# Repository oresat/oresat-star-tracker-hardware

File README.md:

# oresat-star-tracker

This is the repository for all things related to the star tracker system for OreSat. The star tracker takes pictures of the local star field and returns the spacecraft's attitude (which way it's pointed). This is critical for both OreSat Live and the Cirrus Flux Camera missions which require the satellite to be pointed down to a specific location on the ground.

Our hardware is all custom hardware for the open source "OreSat bus" that we're developing. The star tracker is one of our [Octavo OSD3358-1G-ISM](https://octavosystems.com/octavo_products/osd335x-sm/) "Linux box on a Chip" cards, with a custom camera setup based on the [On Semiconductor AR1030](https://www.onsemi.com/pub/Collateral/AR0130CS-D.PDF).

*Looking for what's running on this? Our star tracker software, based on [OpenStarTracker](https://openstartracker.org) from the University at Buffalo, was migrated to the [oresat-star-tracker-software](https://github.com/oresat/oresat-star-tracker-software) repository on 2/21/2020.*
"Looking for pru kernel module / firmware see [oresat-linux-prucam](https://github.com/oresat/oresat-linux-prucam)"

Where to find things:

- oresat-camera-hardware - directories related to hardware for OreSat camera system
- Old stuff
   - STM32F4-camera-system - OreSat camera system based on the STM32F4 MCU
   - archive - old files and projects no longer in use
   - camera_testing - files related to testing our AR0130-based cameras

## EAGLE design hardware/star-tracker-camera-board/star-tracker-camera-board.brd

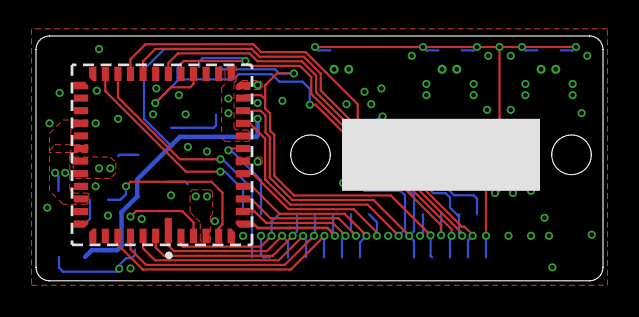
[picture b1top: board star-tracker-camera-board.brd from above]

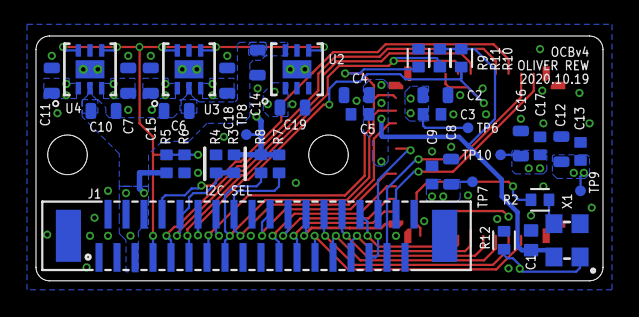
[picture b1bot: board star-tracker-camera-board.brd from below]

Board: 4 copper layers, 31.5 x 13.6 mm, 41 parts (40 on the bottom side), 34 nets.

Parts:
C1: 10nF; .0402-A-NOSILK
C2, C4, C8, C12, C16: 10uF; .0603-C-NOSILK
C3, C5, C9, C13, C17: 0.1uF; .0402-B-NOSILK
C6, C10, C14: 1.0uF; .0603-C-NOSILK
C7, C11, C15, C18, C19: 2.2uF; .0603-C-NOSILK
J1: 3-1734742-6; TE_3-1734742-6
R2: 100; .0402-B
R3, R6: DNP; .0402-B-NOSILK
R4, R5: 10k; .0402-B-NOSILK
R7, R8: 4.7k; .0402-B-NOSILK
R9, R10, R11, R12: 10k; .0402-B
TP6, TP7, TP8, TP9, TP10: TPTP06R; TP06R
U1: AR0134CSSM00SPCA0
U2: TPS70618DRVR; DRV6_1P6X1
U3, U4: TPS71928-28DRVT; DRV6_1P6X1
X1: KC2520B27.0000C10E00; OSC_KYOCERA_KC2520B

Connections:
3.3V: C6.1, C10.1, C14.1, J1.4, J1.5, J1.6, R5.1, U2.6, U3.2, U4.2
!OE: J1.11, R11.1, U1.23
!RESET: J1.13, R9.2, U1.17
CLK_EN: J1.14, R12.2, X1.1
D0: J1.25, U1.45
D1: J1.26, U1.46
D2: J1.27, U1.47
D3: J1.28, U1.48
D4: J1.29, U1.1
D5: J1.30, U1.2
D6: J1.31, U1.3
D7: J1.24, U1.7
D8: J1.23, U1.8
D9: J1.22, U1.9
D10: J1.21, U1.10
D11: J1.20, U1.11
FLASH: J1.9, U1.26
GND: C1.1, C2.2, C3.2, C4.2, C5.2, C6.2, C7.2, C8.2, C9.2, C10.2, C11.2, C12.2, C13.2, C14.2, C15.2, C16.2, C17.2, C18.2, C19.2, J1.1, J1.2, J1.3, J1.17, J1.18, J1.19, J1.35, J1.36, J1.S1, J1.S2, R4.1, R6.2, R9.1, R12.1, U1.6, U1.25, U1.30, U1.35, U1.39, U1.44, U2.2, U2.3, U2.5, U2.7, U2.8, U2.9, U3.5, U3.7, U3.8, U3.9, U4.5, U4.7, U4.8, U4.9, X1.2
HSYNC: J1.34, U1.29
unnamed: R2.1, X1.3
unnamed: R2.2, U1.5
PIXCLK: J1.32, U1.13
SADDR: J1.10, R3.1, R4.2, U1.24
SCLK: J1.16, R7.1, U1.15
SDATA: J1.15, R8.1, U1.16
STANDBY: J1.12, R10.1, U1.22
TRIGGER: J1.8, U1.27
VAA: C11.1, C12.1, C13.1, TP9.TP, U1.34, U1.36, U1.40, U4.1
VAA_PIX: C7.1, C16.1, C17.1, TP10.TP, U1.37, U1.38, U4.3
VDD: C2.1, C3.1, C19.1, TP6.TP, U1.14, U1.19, U2.1
VDD_IO: C1.2, C4.1, C5.1, C18.1, R3.2, R7.2, R8.2, R10.2, R11.2, TP8.TP, U1.12, U1.18, U3.3, X1.4
VDD_PLL: C8.1, C9.1, C15.1, TP7.TP, U1.4, U3.1
VREG_EN: J1.7, R5.2, R6.1, U2.4, U3.4, U3.6, U4.4, U4.6
VSYNC: J1.33, U1.28

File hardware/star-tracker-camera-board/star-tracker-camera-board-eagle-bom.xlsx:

Qty | Value | Device | Package | Parts | Description | DPN | MPN | TP_SIGNAL_NAME | VENDOR
1 | 10nF | C-EU0402-A-NOSILK | .0402-A-NOSILK | C1 | CAPACITOR, European symbol
5 | 10uF | C-EU0603-C-NOSILK | .0603-C-NOSILK | C2, C4, C8, C12, C16 | CAPACITOR, European symbol
5 | 0.1uF | C-EU0402-B-NOSILK | .0402-B-NOSILK | C3, C5, C9, C13, C17 | CAPACITOR, European symbol
3 | 1.0uF | C-EU0603-C-NOSILK | .0603-C-NOSILK | C6, C10, C14 | CAPACITOR, European symbol
5 | 2.2uF | C-EU0603-C-NOSILK | .0603-C-NOSILK | C7, C11, C15, C18, C19 | CAPACITOR, European symbol
1 | 3-1734742-6 | 3-1734742-6 | TE_3-1734742-6 | J1 | 36 Position FFC, FPC Connector Contacts, Vertical, 1 Sided 0.020 (0.50mm) Surfa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 | A100241CT-ND | 3-1734742-6
1 | 100 | R-US_0402-B | .0402-B | R2 | RESISTOR, American symbol
6 | 10k | R-US_0402-B | .0402-B | R4, R5, R9, R10, R11, R12 | RESISTOR, American symbol
2 | 4.7k | R-US_0402-B-NOSILK | .0402-B-NOSILK | R7, R8 | RESISTOR, American symbol
1 | AR0134CSSM00SPCA0 | AR0134CSSM00SPCA0 | AR0134CSSM00SPCA0 | U1
1 | TPS70618DRVR | TPS70618DRVR | DRV6_1P6X1 | U2 |  | 296-48768-1-ND | TPS70618DRVR |  | Texas Instruments
2 | TPS71928-28DRVT | TPS71928-28DRVT | DRV6_1P6X1 | U3, U4 |  | 296-21660-1-ND | TPS71928-28DRVR |  | Texas Instruments
1 | KC2520B27.0000C10E00 | KC2520B27.0000C10E00 | OSC_KYOCERA_KC2520B | X1 |  | 478-4781-1-ND | KC2520B27.0000C10E00 |  | Kyocera

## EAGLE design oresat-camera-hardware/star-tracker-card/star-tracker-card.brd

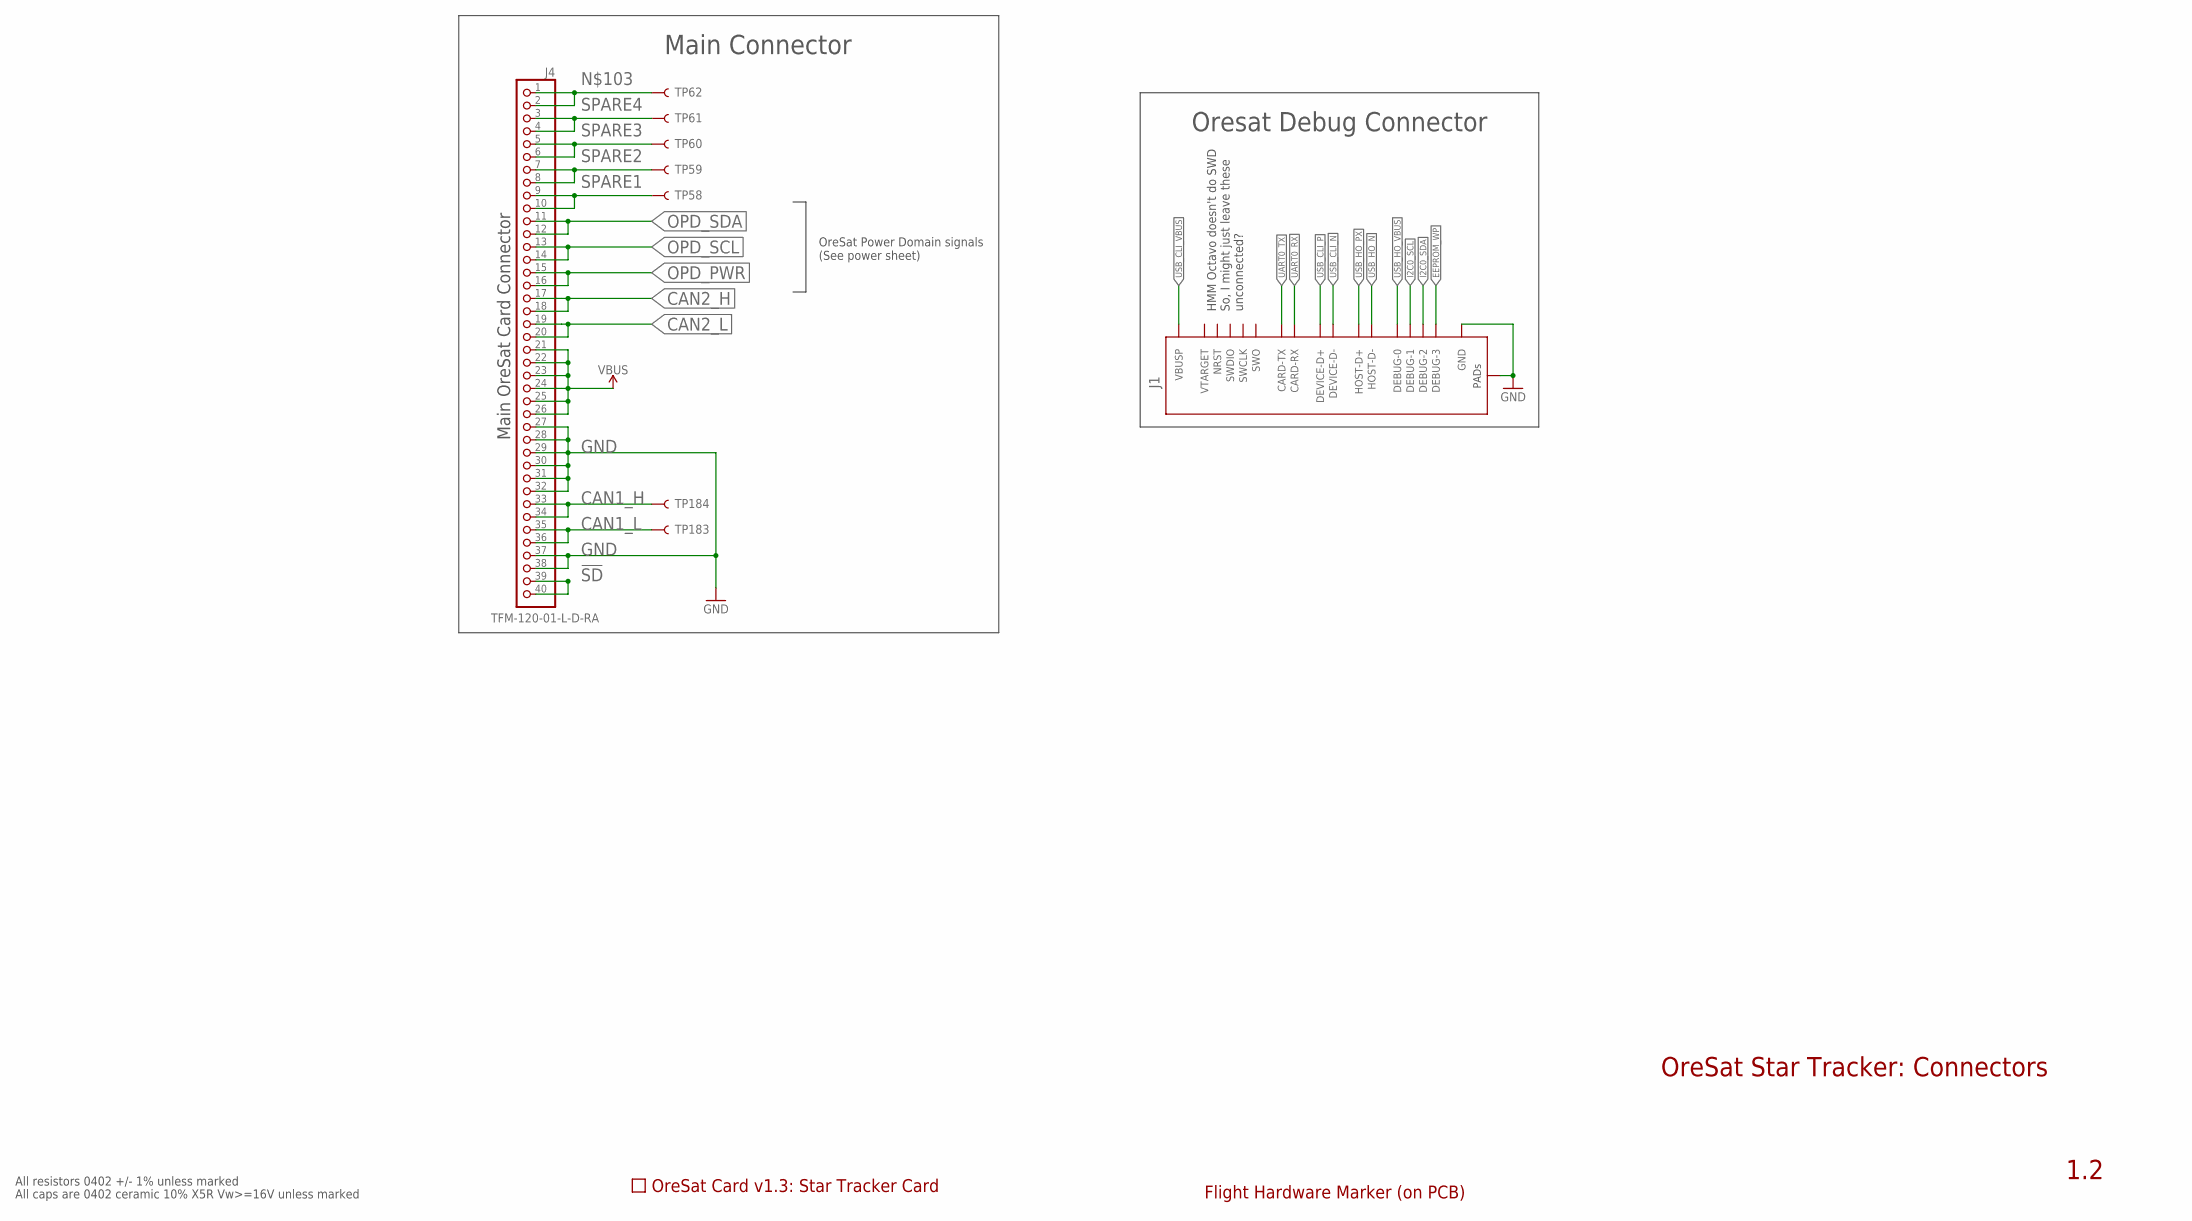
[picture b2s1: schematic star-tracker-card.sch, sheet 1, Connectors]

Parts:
J1: ORESAT-DEBUG-CONNECTOR-CARD; TE_2-1734592-0
J4: TFM-120-01-L-D-RA; J-SAMTEC-TFM-120-X1-XXX-D-RA
PCB1: ORESAT-CARD-V1.3-STAR-TRACKER
TP58, TP59, TP60, TP61, TP62, TP183, TP184: TEST-POINT3X4; PAD.03X.04
U$1: FLIGHMARKERNEW; FLIGHTMARKER_NEW_BOARDS

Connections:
!SD: J4.39, J4.40
CAN1_H: J4.33, J4.34, TP184.P$1
CAN1_L: J4.35, J4.36, TP183.P$1
CAN2_H: J4.17, J4.18; also elsewhere on the board
CAN2_L: J4.19, J4.20; also elsewhere on the board
EEPROM_WP: J1.20 (DEBUG-3); also elsewhere on the board
GND: J1.3 (GND), J1.6 (GND), J1.9 (GND), J1.PAD1 (PAD), J1.PAD2 (PAD), J4.27, J4.28, J4.29, J4.30, J4.31, J4.32, J4.37, J4.38; also elsewhere on the board
I2C0_SCL: J1.18 (DEBUG-1); also elsewhere on the board
I2C0_SDA: J1.19 (DEBUG-2); also elsewhere on the board
unnamed: J4.1, J4.2, TP62.P$1
OPD_PWR: J4.15, J4.16; also elsewhere on the board
OPD_SCL: J4.13, J4.14; also elsewhere on the board
OPD_SDA: J4.11, J4.12; also elsewhere on the board
SPARE1: J4.9, J4.10, TP58.P$1
SPARE2: J4.7, J4.8, TP59.P$1
SPARE3: J4.5, J4.6, TP60.P$1
SPARE4: J4.3, J4.4, TP61.P$1
UART0_RX: J1.12 (CARD-RX); also elsewhere on the board
UART0_TX: J1.13 (CARD-TX); also elsewhere on the board
USB_CLI_N: J1.5 (DEVICE-D-); also elsewhere on the board
USB_CLI_P: J1.4 (DEVICE-D+); also elsewhere on the board
USB_CLI_VBUS: J1.1 (VBUSP), J1.2 (VBUSP); also elsewhere on the board
USB_HO_N: J1.8 (HOST-D-); also elsewhere on the board
USB_HO_PX: J1.7 (HOST-D+); also elsewhere on the board
USB_HO_VBUS: J1.17 (DEBUG-0); also elsewhere on the board
VBUS: J4.21, J4.22, J4.23, J4.24, J4.25, J4.26; also elsewhere on the board

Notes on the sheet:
OreSat Star Tracker: Connectors
1.2
All resistors 0402 +/- 1% unless marked
All caps are 0402 ceramic 10% X5R Vw>=16V unless marked
Main Connector
Main OreSat Card Connector
OreSat Power Domain signals (See power sheet)
HMM Octavo doesn't do SWD So, I might just leave these unconnected?
Oresat Debug Connector

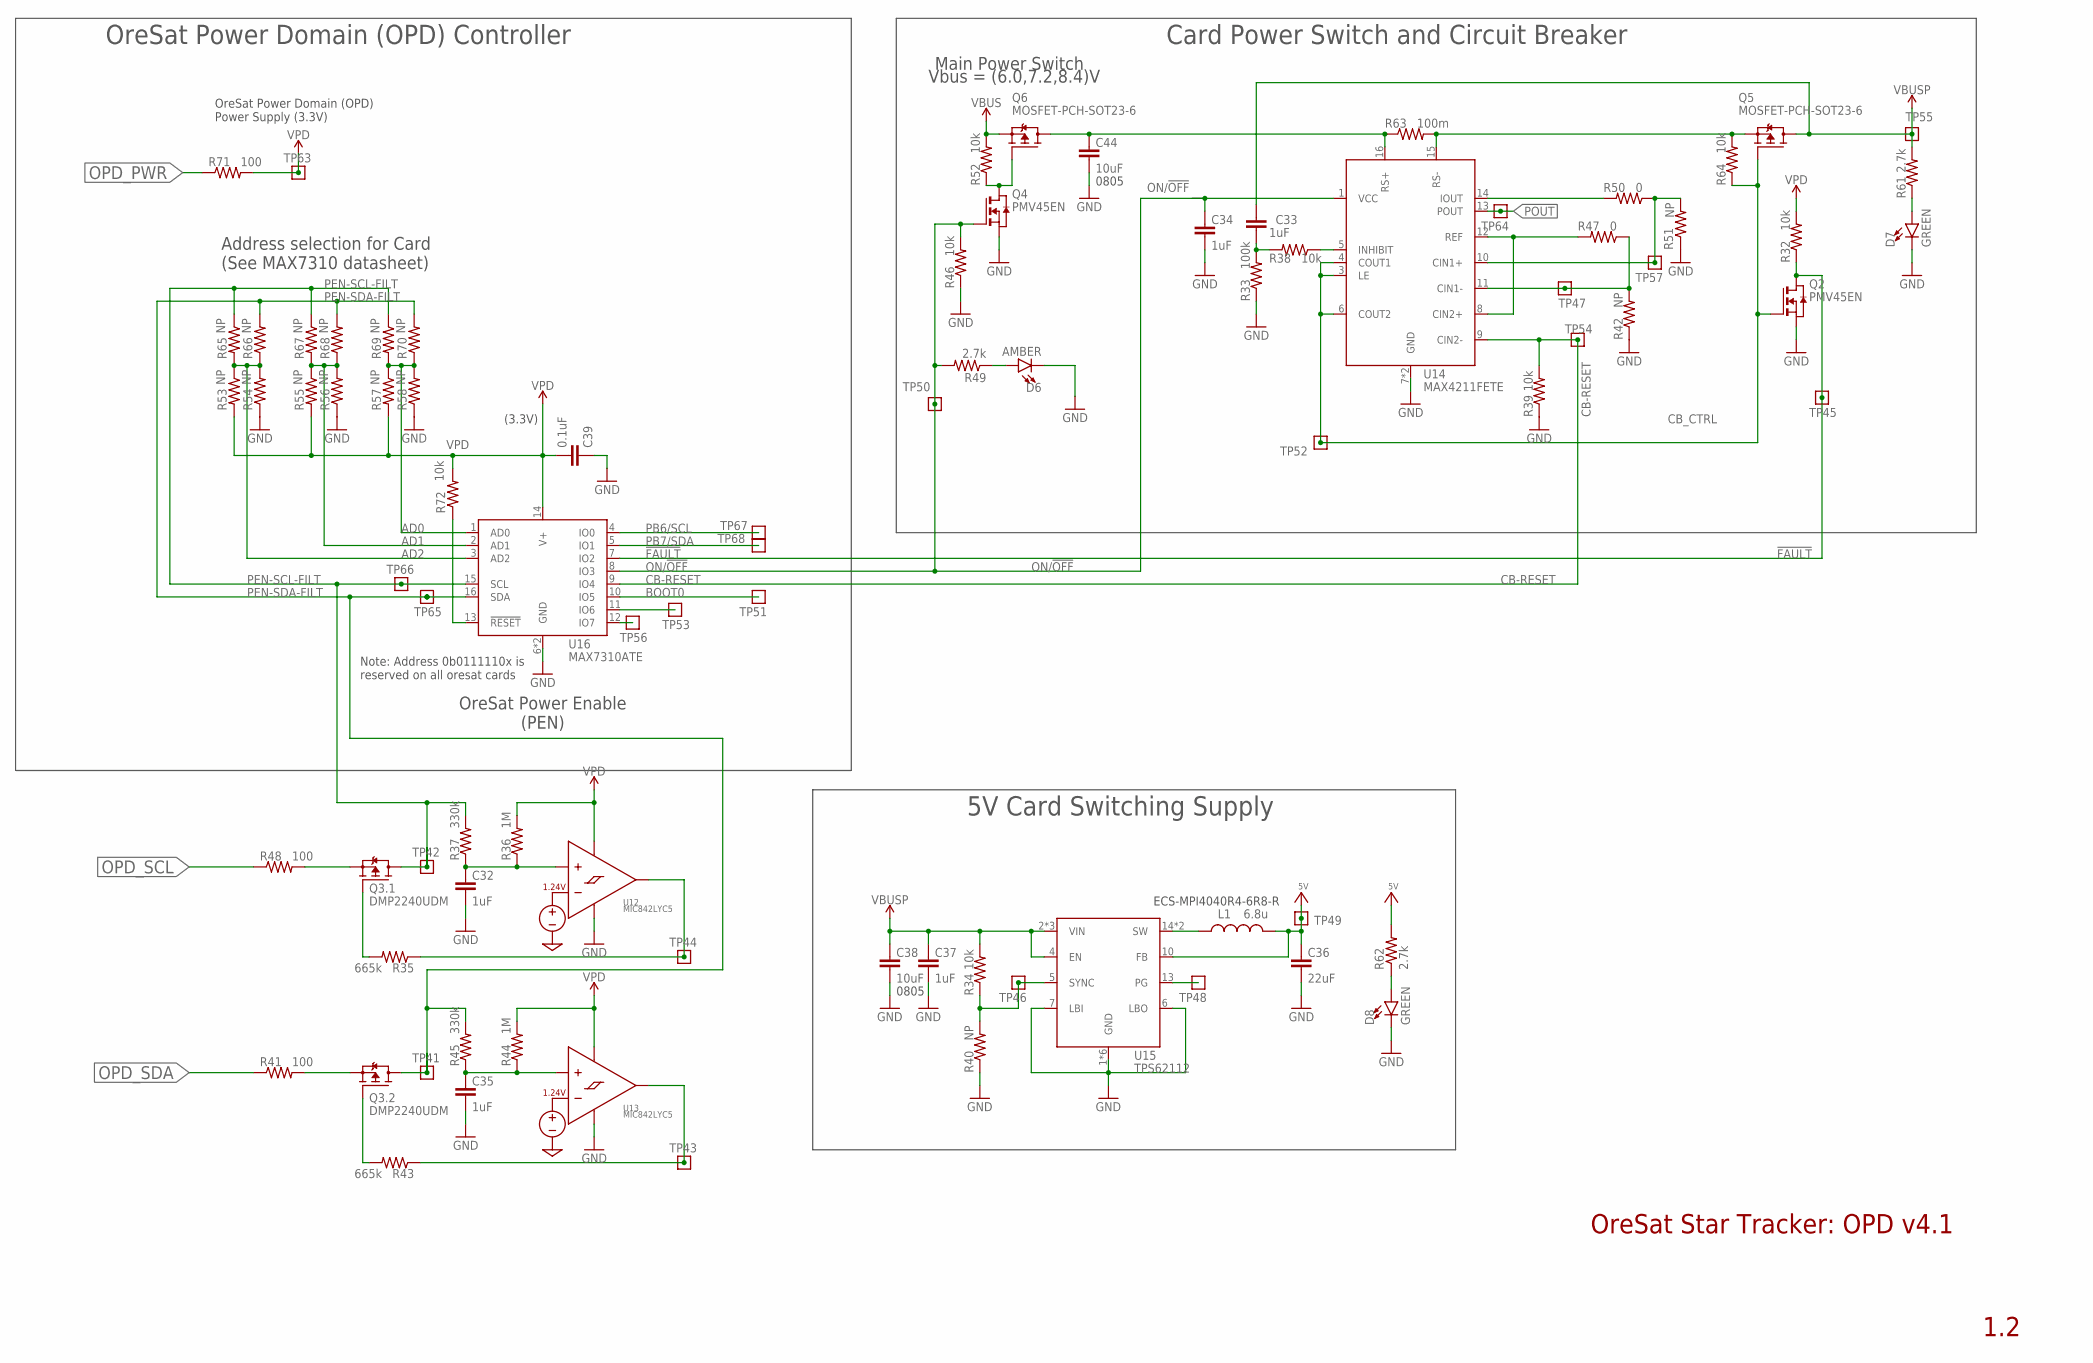
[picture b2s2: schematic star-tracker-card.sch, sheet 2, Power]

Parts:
C32, C35: 1uF; .0805-B-NOSILK
C33: 1uF; .0603-A; MPN CL05B104KO5NNNC
C34, C37: 1uF; .0603-A
C36: 22uF; C1210
C38, C44: 10uF; .0805-B
C39: 0.1uF; .0603-A
D6: AMBER; LED-0603
D7, D8: GREEN; LED-0603
L1: 6.8u; ECS-MPI4040
Q2, Q4: PMV45EN; SOT23; MPN PMV45EN2R
Q3: DMP2240UDM; SOT23-6
Q5, Q6: MOSFET-PCH-SOT23-6; SOT23-6; MPN DMP3050LVT-7
R32, R34, R39, R46, R52, R64, R72: 10k; .0603-A
R33: 100k; .0603-A; MPN RC1005F6653CS
R35, R43: 665k; .0603-A
R36, R44: 1M; .0603-A
R37, R45: 330k; .0603-A
R38: 10k; .0603-A; MPN RC1005F6653CS
R40, R42, R51, R53, R54, R55, R56, R57, R58, R65, R66, R67, R68, R69, R70: NP; .0603-A; MPN RC1005F6653CS
R41, R48, R71: 100; .0603-A
R47, R50: 0; .0603-A
R49, R61, R62: 2.7k; .0603-A
R63: 100m; R1206
TP41, TP42, TP43, TP44, TP45, TP46, TP47, TP48, TP49, TP50, TP51, TP52, TP53, TP54, TP55, TP56, TP57, TP63, TP64, TP65, TP66, TP67, TP68: TEST-POINT; 2MM-TEST-POINT
U12, U13: MIC842LYC5; SC70-5
U14: MAX4211FETE; QFN65P400X400X80-17T210
U15: TPS62112; S-PVQFN-16
U16: MAX7310ATE; QFN65P400X400X80-17T210; MPN MAX7310ATE

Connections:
5V: C36.1, L1.2, R62.2, TP49.1, U15.10 (FB); also elsewhere on the board
!FAULT: Q2.3 (D), R32.1, TP45.1, U16.7 (IO2)
AD0: R57.1, R58.2, R69.2, R70.1, U16.1 (AD0)
AD1: R55.1, R56.2, R67.2, R68.1, U16.2 (AD1)
AD2: R53.1, R54.2, R65.2, R66.1, U16.3 (AD2)
BOOT0: TP51.1, U16.10 (IO5)
CB-RESET: R39.2, TP54.1, U14.9 (CIN2-), U16.9 (IO4)
CB_CTRL: Q2.1 (G), Q5.3 (G), R64.1, TP52.1, U14.3 (LE), U14.4 (COUT1), U14.6 (COUT2)
GND: C32.2, C34.2, C35.2, C36.2, C37.2, C38.2, C39.1, C44.2, D6.C, D7.C, D8.C, Q2.2 (S), Q4.2 (S), R33.1, R39.1, R40.1, R42.1, R46.1, R51.1, R54.1, R56.1, R58.1, U12.2 (GND), U13.2 (GND), U14.7 (GND), U14.EPAD (GND), U15.1 (GND), U15.6 (LBO), U15.7 (LBI), U15.9 (GND), U15.11 (GND), U15.12 (GND), U15.16 (GND), U15.PAD (GND), U16.6 (GND), U16.EPAD (GND); also elsewhere on the board
IOUT: R50.2, U14.14 (IOUT)
unnamed: C32.1, R36.1, R37.1, U12.1 (INP)
unnamed: R35.1, TP44.1, U12.4 (OUT)
unnamed: TP56.1, U16.12 (IO7)
unnamed: C44.1, Q6.1 (D), Q6.2 (D), Q6.5 (D), Q6.6 (D), R63.1, U14.16 (RS+)
unnamed: Q5.4 (S), R63.2, R64.2, U14.15 (RS-)
unnamed: C35.1, R44.1, R45.1, U13.1 (INP)
unnamed: Q3.3 (G), R43.2
unnamed: Q3.1 (G), R35.2
unnamed: D7.A, R61.1
unnamed: D8.A, R62.1
unnamed: TP53.1, U16.11 (IO6)
unnamed: Q3.5 (S), R48.2
unnamed: D6.A, R49.1
unnamed: Q3.2 (S), R41.2
unnamed: R43.1, TP43.1, U13.4 (OUT)
unnamed: R72.1, U16.13 (!RESET)
unnamed: Q4.3 (D), Q6.3 (G), R52.1
unnamed: R50.1, R51.2, TP57.1, U14.10 (CIN1+)
unnamed: R42.2, R47.1, TP47.1, U14.11 (CIN1-)
unnamed: R47.2, U14.8 (CIN2+), U14.12 (REF)
unnamed: C33.1, R33.2, R38.2
unnamed: R38.1, U14.5 (INHIBIT)
ON/!OFF: C34.1, Q4.1 (G), R46.2, R49.2, TP50.1, U14.1 (VCC), U16.8 (IO3)
OPD_PWR: R71.1; also elsewhere on the board
OPD_SCL: R48.1; also elsewhere on the board
OPD_SDA: R41.1; also elsewhere on the board
PB6/SCL: TP67.1, U16.4 (IO0)
PB7/SDA: TP68.1, U16.5 (IO1)
PEN-SCL-FILT: Q3.6 (D), R37.2, R65.1, R67.1, R69.1, TP42.1, TP66.1, U16.15 (SCL)
PEN-SDA-FILT: Q3.4 (D), R45.2, R66.2, R68.2, R70.2, TP41.1, TP65.1, U16.16 (SDA)
POUT: TP64.1, U14.13 (POUT)
TPS62111-PG: TP48.1, U15.13 (PG)
TPS62111-SYNC: R34.1, R40.2, TP46.1, U15.5 (SYNC)
TPS62111_SW: L1.1, U15.14 (SW), U15.15 (SW)
VBUS: Q6.4 (S), R52.2; also elsewhere on the board
VBUSP: C33.2, C37.1, C38.1, Q5.1 (D), Q5.2 (D), Q5.5 (D), Q5.6 (D), R34.2, R61.2, TP55.1, U15.2 (VIN), U15.3 (VIN), U15.4 (EN), U15.8 (VIN)
VPD: C39.2, R32.2, R36.2, R44.2, R53.2, R55.2, R57.2, R71.2, R72.2, TP63.1, U12.5 (VDD), U13.5 (VDD), U16.14 (V+)

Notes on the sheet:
0805
ECS-MPI4040R4-6R8-R
5V Card Switching Supply
1.2
Main Power Switch
OreSat Power Enable (PEN)
Address selection for Card (See MAX7310 datasheet)
(3.3V)
Vbus = (6.0,7.2,8.4)V
OreSat Power Domain (OPD) Power Supply (3.3V)
OreSat Power Domain (OPD) Controller
Card Power Switch and Circuit Breaker
Note: Address 0b0111110x is reserved on all oresat cards
OreSat Star Tracker: OPD v4.1

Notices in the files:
STM32F4-camera-system/stm32-camera/src/main.c:
© Portions COPYRIGHT 2011 STMicroelectronics
© Portions COPYRIGHT 2012 Embest Tech. Co., Ltd.
parts and their libraries:
SparkFun-PowerSymbols: Licensing: Creative Commons ShareAlike 4.0 International - https://creativecommons.org/licenses/by-sa/4.0
SparkFun-Passives: Licensing: CC v3.0 Share-Alike You are welcome to use this library for commercial purposes.
